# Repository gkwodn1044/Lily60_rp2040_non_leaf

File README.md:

HJGing님의 KPRP 프로젝트중 [Lily60_rp2040](https://github.com/Keyboard-PCB-Replica-Project/Lily60_rp2040.git) repo를 fork하여 non leaf 버전으로 수정한 PCB입니다. 

GOK Lily 레플리카 PCB입니다.

추후에 인디케이터용 RGB LED나 SMD LED가 추가될 수도 있습니다.

(현재는 백색 2핀 LED와 오른쪽 아래 LED만 구현해 두었습니다.)

추가 필요 부품 : 

작동 확인 여부 : X

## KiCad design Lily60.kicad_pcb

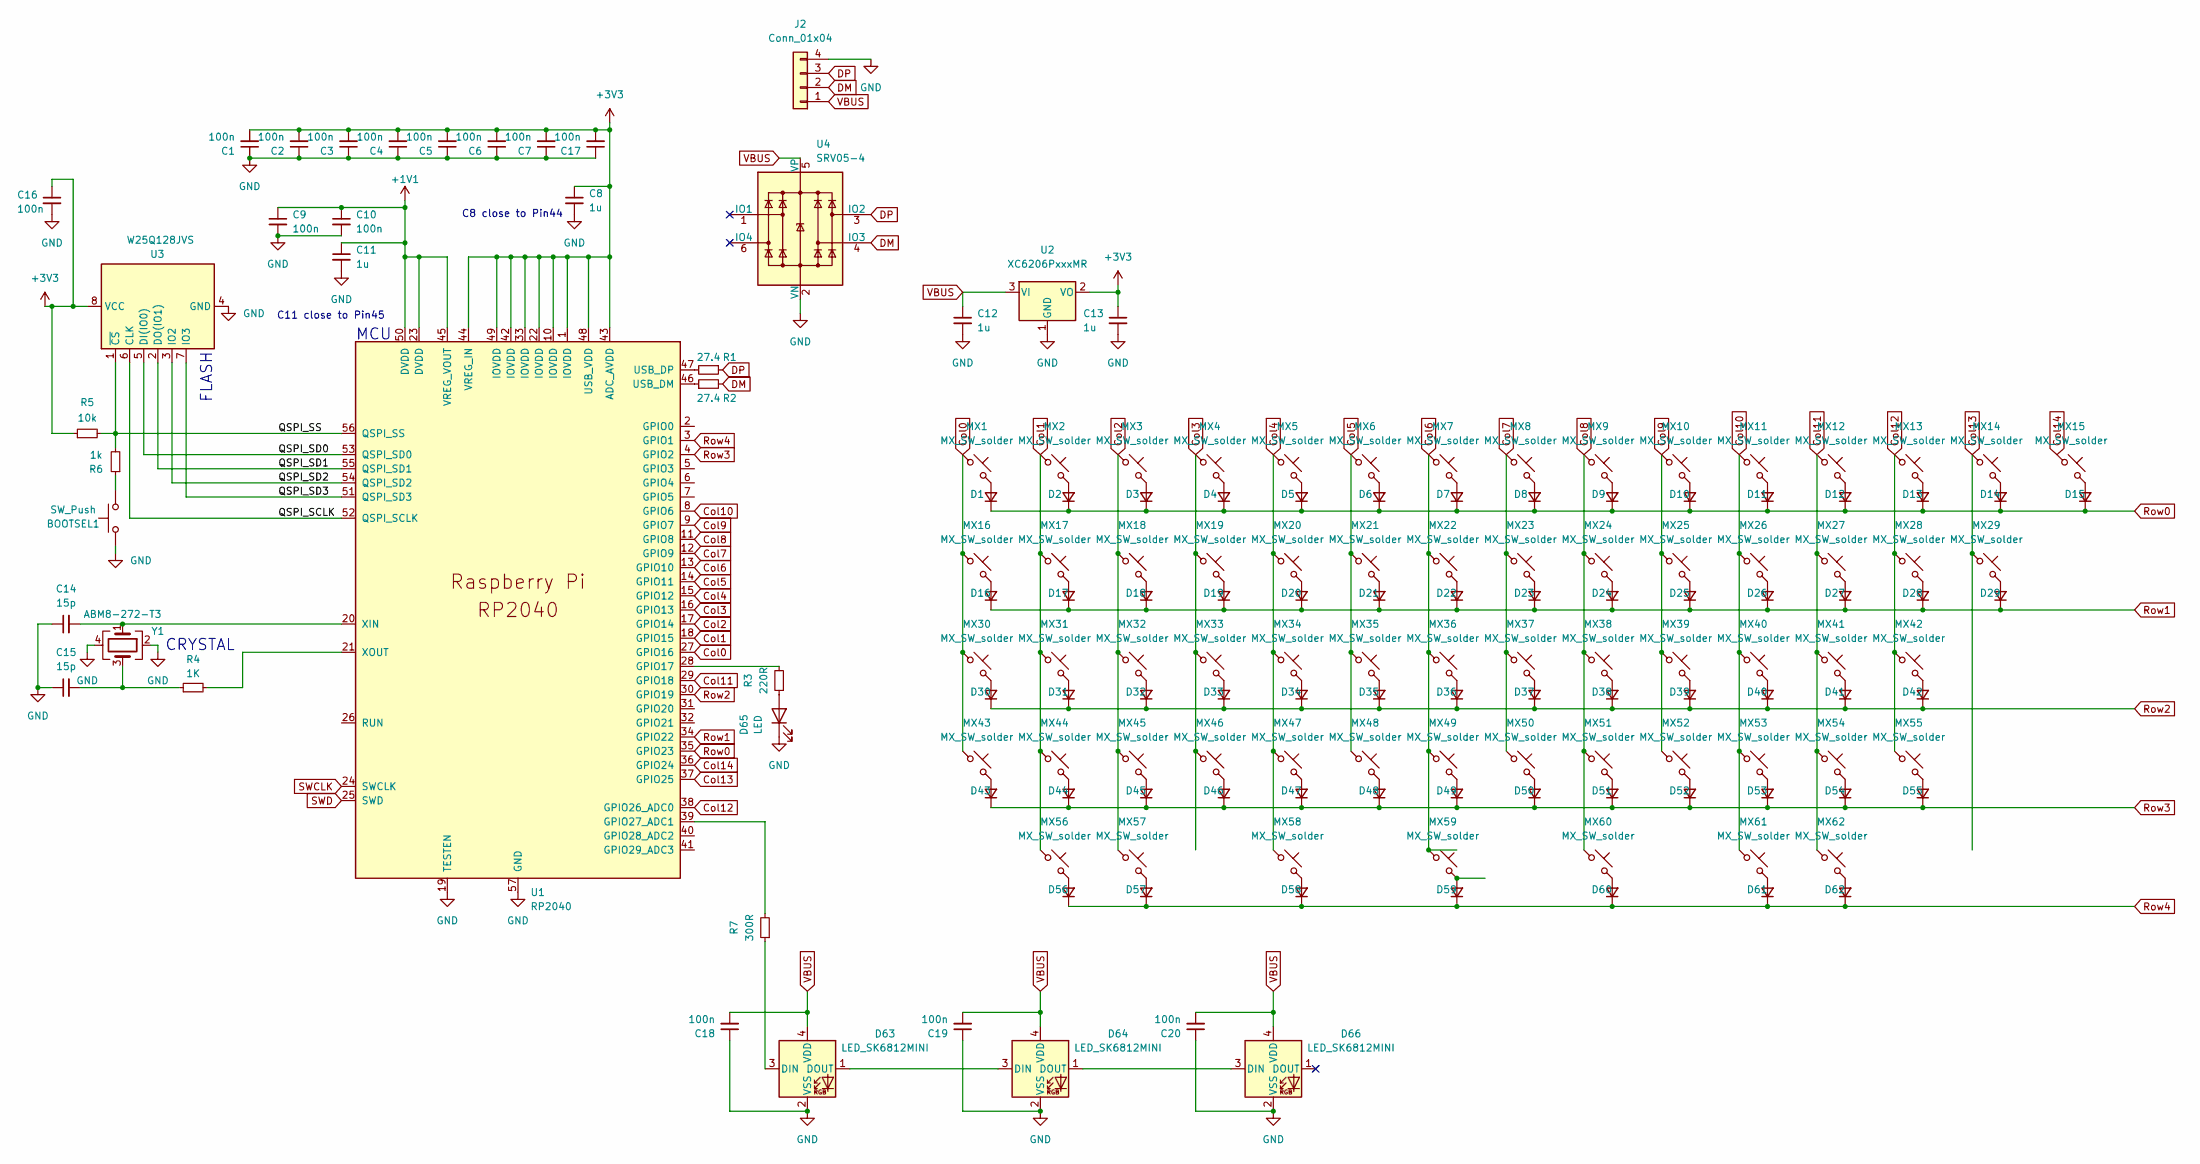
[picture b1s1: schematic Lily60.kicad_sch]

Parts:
BOOTSEL1: SW_Push; SW_Push_1P1T_XKB_TS-1187A
C1, C2, C3, C4, C5, C6, C7, C9, C10, C16, C17, C18, C19, C20: 100n; C_0402_1005Metric
C8, C11, C12, C13: 1u; C_0402_1005Metric
C14, C15: 15p; C_0402_1005Metric
D1, D2, D3, D4, D5, D6, D7, D8, D9, D10, D11, D12, D13, D14, D15, D16, D17, D18, D19, D20, D21, D22, D23, D24, D25, D26, D27, D28, D29, D30, D31, D32, D33, D34, D35, D36, D37, D38, D39, D40, D41, D42, D43, D44, D45, D46, D47, D48, D49, D50, D51, D52, D53, D54, D55, D56, D57, D58, D59, D60, D61, D62: D_Small; Diode_SOD-123_noref2
D63, D64, D66: LED_SK6812MINI; LED_SK6812MINI-E_clrce
D65: LED; cherry_ledhole
J2: Conn_01x04; JST_SH_SM04B-SRSS-TB_1x04-1MP_P1.00mm_Horizontal
MX1, MX2, MX3, MX4, MX5, MX6, MX7, MX8, MX9, MX10, MX11, MX12, MX13, MX14, MX15, MX16, MX17, MX18, MX19, MX20, MX21, MX22, MX23, MX24, MX25, MX26, MX27, MX28, MX29, MX30, MX31, MX32, MX33, MX34, MX35, MX36, MX37, MX38, MX39, MX40, MX41, MX42, MX43, MX44, MX45, MX46, MX47, MX48, MX49, MX50, MX51, MX52, MX53, MX54, MX55, MX56, MX57, MX58, MX59, MX60, MX61, MX62: MX_SW_solder; MX_PCB_1.00u_NoSilkscreen3
R1, R2: 27.4; C_0603_1608Metric
R3: 220R; C_0402_1005Metric_noref
R4: 1K; C_0402_1005Metric
R5: 10k; C_0402_1005Metric
R6: 1k; C_0402_1005Metric
R7: 300R; C_0402_1005Metric
U1: RP2040; RP2040-QFN-56
U2: XC6206PxxxMR; SOT-23
U3: W25Q128JVS; SOIC-8_5.23x5.23mm_P1.27mm
U4: SRV05-4; SOT-23-6
Y1: ABM8-272-T3; Oscillator_SMD_EuroQuartz_XO32-4Pin_3.2x2.5mm

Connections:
+1V1: C9.1, C10.1, C11.1, U1.23 (DVDD), U1.45 (VREG_VOUT), U1.50 (DVDD)
+3V3: C1.2, C2.2, C3.2, C4.2, C5.2, C6.2, C7.2, C8.1, C13.1, C16.1, C17.2, R5.1, U1.1 (IOVDD), U1.10 (IOVDD), U1.22 (IOVDD), U1.33 (IOVDD), U1.42 (IOVDD), U1.43 (ADC_AVDD), U1.44 (VREG_IN), U1.48 (USB_VDD), U1.49 (IOVDD), U2.2 (VO), U3.8 (VCC)
/QSPI_SCLK: U1.52 (QSPI_SCLK), U3.6 (CLK)
/QSPI_SD0: U1.53 (QSPI_SD0), U3.5 (DI(IO0))
/QSPI_SD1: U1.55 (QSPI_SD1), U3.2 (DO(IO1))
/QSPI_SD2: U1.54 (QSPI_SD2), U3.3 (IO2)
/QSPI_SD3: U1.51 (QSPI_SD3), U3.7 (IO3)
/QSPI_SS: R5.2, R6.2, U1.56 (QSPI_SS), U3.1 (~CS)
Col0: MX1.1, MX16.1, MX30.1, MX43.1, U1.27 (GPIO16)
Col1: MX2.1, MX17.1, MX31.1, MX44.1, MX56.1, U1.18 (GPIO15)
Col2: MX3.1, MX18.1, MX32.1, MX45.1, MX57.1, U1.17 (GPIO14)
Col3: MX4.1, MX19.1, MX33.1, MX46.1, U1.16 (GPIO13)
Col4: MX5.1, MX20.1, MX34.1, MX47.1, MX58.1, U1.15 (GPIO12)
Col5: MX6.1, MX21.1, MX35.1, MX48.1, U1.14 (GPIO11)
Col6: MX7.1, MX22.1, MX36.1, MX49.1, MX59.1, U1.13 (GPIO10)
Col7: MX8.1, MX23.1, MX37.1, MX50.1, U1.12 (GPIO9)
Col8: MX9.1, MX24.1, MX38.1, MX51.1, MX60.1, U1.11 (GPIO8)
Col9: MX10.1, MX25.1, MX39.1, MX52.1, U1.9 (GPIO7)
Col10: MX11.1, MX26.1, MX40.1, MX53.1, MX61.1, U1.8 (GPIO6)
Col11: MX12.1, MX27.1, MX41.1, MX54.1, MX62.1, U1.29 (GPIO18)
Col12: MX13.1, MX28.1, MX42.1, MX55.1, U1.38 (GPIO26_ADC0)
Col13: MX14.1, MX29.1, U1.37 (GPIO25)
Col14: MX15.1, U1.36 (GPIO24)
DM: J2.2, R2.2, U4.4 (IO3)
DP: J2.3, R1.1, U4.3 (IO2)
GND: BOOTSEL1.1, C1.1, C2.1, C3.1, C4.1, C5.1, C6.1, C7.1, C8.2, C9.2, C10.2, C11.2, C12.2, C13.2, C14.1, C15.1, C16.2, C17.1, C18.1, C19.1, C20.1, D63.2 (VSS), D64.2 (VSS), D65.1 (K), D66.2 (VSS), J2.4, U1.19 (TESTEN), U1.57 (GND), U2.1 (GND), U3.4 (GND), U4.2 (VN), Y1.2, Y1.4
unnamed: BOOTSEL1.2, R6.1
unnamed: C15.2, R4.1, Y1.3
unnamed: D1.2 (A), MX1.2
unnamed: D2.2 (A), MX2.2
unnamed: D3.2 (A), MX3.2
unnamed: D4.2 (A), MX4.2
unnamed: D5.2 (A), MX5.2
unnamed: D6.2 (A), MX6.2
unnamed: D7.2 (A), MX7.2
unnamed: D8.2 (A), MX8.2
unnamed: D9.2 (A), MX9.2
unnamed: D10.2 (A), MX10.2
unnamed: D11.2 (A), MX11.2
unnamed: D12.2 (A), MX12.2
unnamed: D13.2 (A), MX13.2
unnamed: D14.2 (A), MX14.2
unnamed: D15.2 (A), MX15.2
unnamed: D16.2 (A), MX16.2
unnamed: D17.2 (A), MX17.2
unnamed: D18.2 (A), MX18.2
unnamed: D19.2 (A), MX19.2
unnamed: D20.2 (A), MX20.2
unnamed: D21.2 (A), MX21.2
unnamed: D22.2 (A), MX22.2
unnamed: D23.2 (A), MX23.2
unnamed: D24.2 (A), MX24.2
unnamed: D25.2 (A), MX25.2
unnamed: D26.2 (A), MX26.2
unnamed: D27.2 (A), MX27.2
unnamed: D28.2 (A), MX28.2
unnamed: D29.2 (A), MX29.2
unnamed: D30.2 (A), MX30.2
unnamed: D31.2 (A), MX31.2
unnamed: D32.2 (A), MX32.2
unnamed: D33.2 (A), MX33.2
unnamed: D34.2 (A), MX34.2
unnamed: D35.2 (A), MX35.2
unnamed: D36.2 (A), MX36.2
unnamed: D37.2 (A), MX37.2
unnamed: D38.2 (A), MX38.2
unnamed: D39.2 (A), MX39.2
unnamed: D40.2 (A), MX40.2
unnamed: D41.2 (A), MX41.2
unnamed: D42.2 (A), MX42.2
unnamed: D43.2 (A), MX43.2
unnamed: D44.2 (A), MX44.2
unnamed: D45.2 (A), MX45.2
unnamed: D46.2 (A), MX46.2
unnamed: D47.2 (A), MX47.2
unnamed: D48.2 (A), MX48.2
unnamed: D49.2 (A), MX49.2
unnamed: D50.2 (A), MX50.2
unnamed: D51.2 (A), MX51.2
unnamed: D52.2 (A), MX52.2
unnamed: D53.2 (A), MX53.2
unnamed: D54.2 (A), MX54.2
unnamed: D55.2 (A), MX55.2
unnamed: D56.2 (A), MX56.2
unnamed: D57.2 (A), MX57.2
unnamed: D58.2 (A), MX58.2
unnamed: D59.2 (A), MX59.2
unnamed: D60.2 (A), MX60.2
unnamed: D61.2 (A), MX61.2
unnamed: D62.2 (A), MX62.2
unnamed: D63.3 (DIN), R7.1
unnamed: D63.1 (DOUT), D64.3 (DIN)
unnamed: D64.1 (DOUT), D66.3 (DIN)
unnamed: D65.2 (A), R3.1
unnamed: R3.2, U1.28 (GPIO17)
unnamed: R7.2, U1.39 (GPIO27_ADC1)
unnamed: R2.1, U1.46 (USB_DM)
unnamed: R1.2, U1.47 (USB_DP)
unnamed: C14.2, U1.20 (XIN), Y1.1
unnamed: R4.2, U1.21 (XOUT)
Row0: D1.1 (K), D2.1 (K), D3.1 (K), D4.1 (K), D5.1 (K), D6.1 (K), D7.1 (K), D8.1 (K), D9.1 (K), D10.1 (K), D11.1 (K), D12.1 (K), D13.1 (K), D14.1 (K), D15.1 (K), U1.35 (GPIO23)
Row1: D16.1 (K), D17.1 (K), D18.1 (K), D19.1 (K), D20.1 (K), D21.1 (K), D22.1 (K), D23.1 (K), D24.1 (K), D25.1 (K), D26.1 (K), D27.1 (K), D28.1 (K), D29.1 (K), U1.34 (GPIO22)
Row2: D30.1 (K), D31.1 (K), D32.1 (K), D33.1 (K), D34.1 (K), D35.1 (K), D36.1 (K), D37.1 (K), D38.1 (K), D39.1 (K), D40.1 (K), D41.1 (K), D42.1 (K), U1.30 (GPIO19)
Row3: D43.1 (K), D44.1 (K), D45.1 (K), D46.1 (K), D47.1 (K), D48.1 (K), D49.1 (K), D50.1 (K), D51.1 (K), D52.1 (K), D53.1 (K), D54.1 (K), D55.1 (K), U1.4 (GPIO2)
Row4: D56.1 (K), D57.1 (K), D58.1 (K), D59.1 (K), D60.1 (K), D61.1 (K), D62.1 (K), U1.3 (GPIO1)
SWCLK: U1.24 (SWCLK)
SWD: U1.25 (SWD)
VBUS: C12.1, C18.2, C19.2, C20.2, D63.4 (VDD), D64.4 (VDD), D66.4 (VDD), J2.1, U2.3 (VI), U4.5 (VP)

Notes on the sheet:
C11 close to Pin45
MCU
CRYSTAL
C8 close to Pin44
FLASH

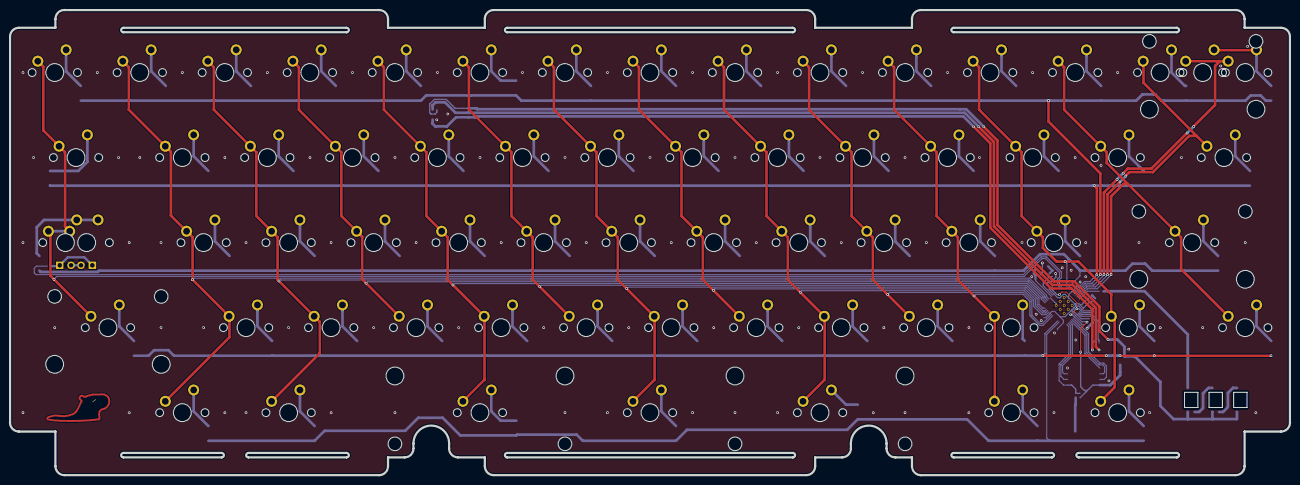
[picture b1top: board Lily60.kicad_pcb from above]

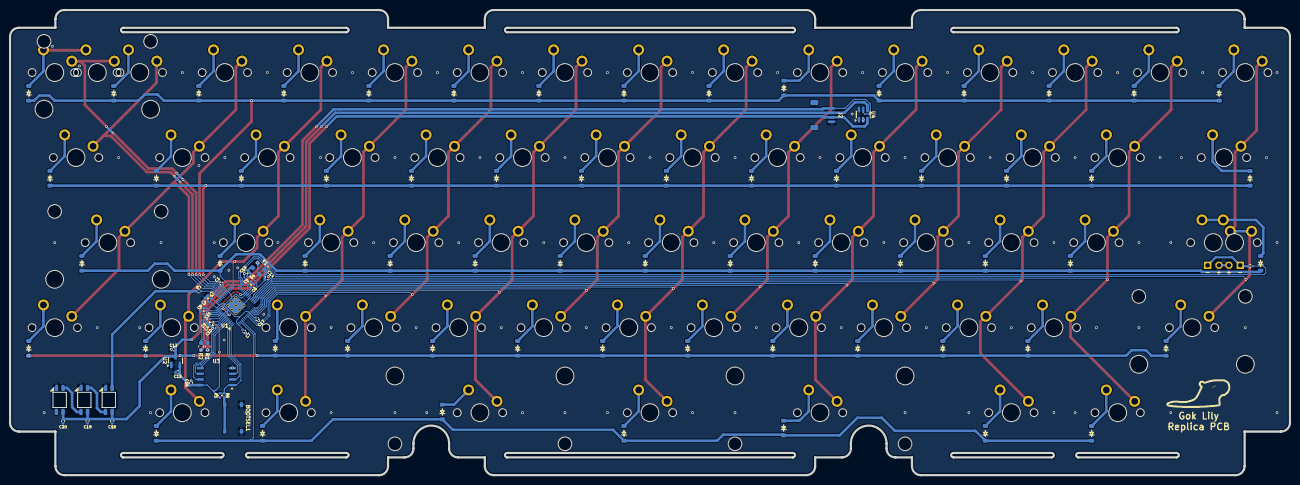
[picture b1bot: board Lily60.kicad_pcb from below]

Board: 2 copper layers, 286.8 x 104.2 mm, 162 parts (96 on the bottom side), 106 nets.

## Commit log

2025-07-04 V1.0
2025-07-05 V1.1
2025-07-05 V1.2
2025-09-03 change the PCB shape to non leaf version
2025-09-03 new gerber file is plotted. original one is gerber.zip.bak
